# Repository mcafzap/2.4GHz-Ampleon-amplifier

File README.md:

# This amplifier is based on the Ampleon BCP2425M9X2S250-1 pallet

The bias circuit is taken from Ampleon's application note AN10900. There is an MSP430G2553 processor and an I2C 1.3" OLED display and 2 digital current monitors using the TLI4970. Unfortunately this current measurement device is end-of life, but it remains the best for resolving 6.25mA and measuring up to 25A. The display monitors voltage & current of each stage, sets the bias of each stage and shows the total power used.

Output protection is provided by a 100W isolator from Bert Modderman (pe1rki.com)
A 30v, 10A supply should give about 150W maximum - more than adequate for Q0-100 access. This pallet has 30dB of gain but a pre-amp will likely be required - the Amsat kit or a cheap shielded Chinese type. The circuit board uses an LM2596 dc-dc module. This can supply 12v for fans and/or the pre-amp or any voltage may be set to suit these devices. A lower voltage will lower the stress on the 3.3v linear regulator.

I used Kicad to draw/plot the circuit board and had them manufactured by JLCPCB. The program was written and tested on TI's Code Composer Studio but Energia may be used. 
The metal work was designed on FreeCAD and can be made from stock Al bar (10mm x 20mm) and Al sheet (2mm). The heatspreader is 10mm x 100mm x 72mm Cu. This is mounted on an Al heatsink approximately 250mm x 200mm x 40mm; it does not seem to require any fans.

Remember this is high frequency so everything must be kept short or shielded and properly 50 ohm terminated.

Thanks go to Vincent(M0LCR), Mike(G4VSS) and Brian(G4EWJ) for software/hardware advice but thanks are especially owed to Anthony Tognarelli of Waterfield Electronics Ltd. (waterfieldelectronics.com) for providing the pallets.

If I were to do this again? I'd simply use multi-turn presets to set the bias levels, (10K across a 3.3v supply). Much of the circuitry is concerned with displaying little-used data like power input and bias currents - once set, these are never changed.

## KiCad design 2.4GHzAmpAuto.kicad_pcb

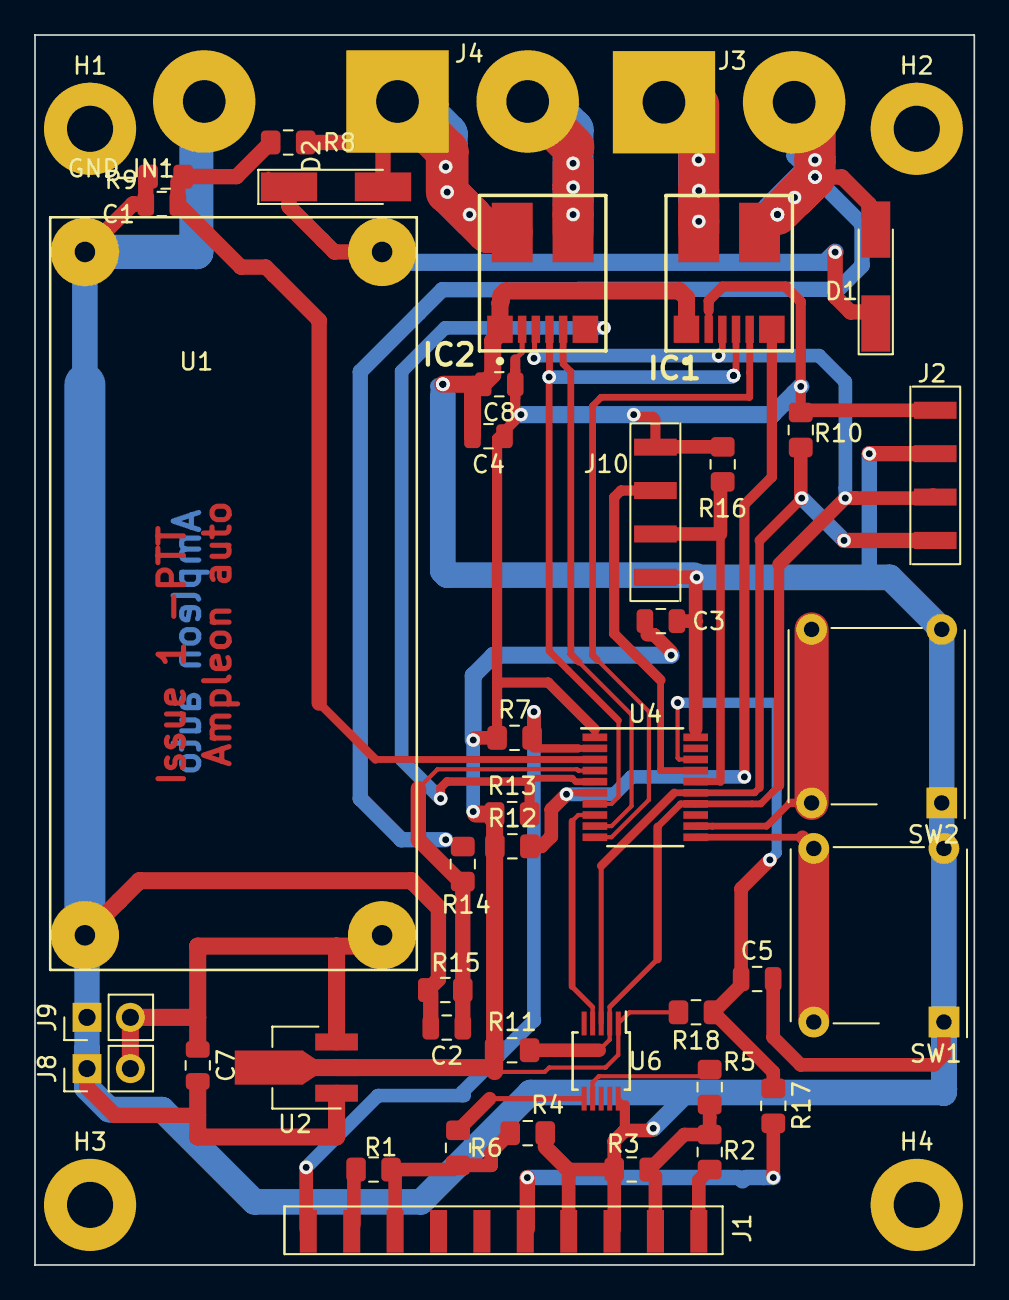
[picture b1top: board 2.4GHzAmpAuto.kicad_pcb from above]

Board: 2 copper layers, 55.0 x 72.0 mm, 47 parts (0 on the bottom side), 31 nets.

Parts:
C1, C2, C3, C4, C5, C8: 0u1; C_0805_2012Metric
C7: 10u; C_0805_2012Metric
D1, D2: D_ALT; D_MiniMELF_Handsoldering
GND_IN1: wire; SolderWirePad_1x01_Drill2.5mm
H1, H2, H3, H4: MountingHole_Pad; MountingHole_2.7mm_M2.5_Pad
IC1, IC2: TLI4970D025T5XUMA1; PG-TISON-8-1
J1: conections to module; Harwin_M20-89010xx_1x10_P2.54mm_Horizontal
J2: OLED; 1x04_P2.54mm_Pads
J3: current A; SolderWirePad_1x02_P7.62mm_Drill2.5mm
J4: current B; SolderWirePad_1x02_P7.62mm_Drill2.5mm
J8: Fan1; PinHeader_1x02_P2.54mm_Vertical
J9: Fan2; PinHeader_1x02_P2.54mm_Vertical
J10: program port; 1x04_P2.54mm_Pads
R1: 2K7; R_0805_2012Metric_Pad1.15x1.40mm_HandSolder
R2, R7: 1K5; R_0805_2012Metric_Pad1.15x1.40mm_HandSolder
R3: 1K0; R_0805_2012Metric_Pad1.15x1.40mm_HandSolder
R4: 4K3; R_0805_2012Metric_Pad1.15x1.40mm_HandSolder
R5, R17: K33; R_0805_2012Metric_Pad1.15x1.40mm_HandSolder
R6: K56; R_0805_2012Metric_Pad1.15x1.40mm_HandSolder
R8, R14: 33K; R_0805_2012Metric_Pad1.15x1.40mm_HandSolder
R9, R15: 2K2; R_0805_2012Metric_Pad1.15x1.40mm_HandSolder
R10, R11, R12, R13: 4K7; R_0805_2012Metric_Pad1.15x1.40mm_HandSolder
R16, R18: 10K; R_0805_2012Metric_Pad1.15x1.40mm_HandSolder
SW1, SW2: SW_Push; SW_MEC_5GTH9
U1: LM2596dcdc; LM2596_dc-dc_module
U2: AZ1117-3.3; SOT-89-3_Handsoldering
U4: MSP430G2553IPW20; TSSOP-20_4.4x6.5mm_P0.65mm
U6: MCP4728; MSOP-10_3x3mm_P0.5mm

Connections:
/12v: C7.1, J8.2, J9.2, U1.4, U2.3
/+3v3: C3.1, C4.1, C8.1, IC1.2, IC2.2, J2.1, J10.4, R7.1, R10.1, R11.1, R12.1, R13.1, R16.1, R18.2, U2.2, U4.1, U6.1
/GND: C1.2, C2.2, C3.2, C4.2, C5.2, C7.2, C8.2, GND_IN1.1, H1.1, H2.1, H3.1, H4.1, IC1.1, IC2.1, J1.3, J1.4, J2.2, J8.1, J9.1, J10.1, R3.2, R4.2, R9.2, R15.2, SW1.1, SW2.1, U1.2, U1.3, U2.1, U4.20, U6.10
/PTT: J1.5, R17.2
/T1: J1.1, R2.1
/T2: J1.9, R1.2
/T3: J1.10, R7.2, U4.2
/VG1: J1.2, R2.2, R3.1, R5.2
/VG2: J1.8, R1.1, R4.1, R6.2
/Vdd: D1.1, D2.1, U1.1
/reset: J10.2, R16.2, U4.16
/scl: IC1.3, IC2.3, J2.3, R11.2, U4.14, U6.2
/sda: J2.4, R10.2, U4.15, U6.3
/test: J10.3, U4.17
unnamed: C1.1, R8.2, R9.1, U4.3
unnamed: C2.1, R14.2, R15.1, U4.4
unnamed: C5.1, R17.1, R18.1, U4.18
unnamed: D1.2, IC1.7, J3.2, R14.1
unnamed: D2.2, IC2.8, J4.1, R8.1
unnamed: IC1.4, IC2.4, U4.7
unnamed: IC1.5, U4.10
unnamed: IC1.6, R12.2, U4.6
unnamed: IC1.8, J3.1
unnamed: IC2.5, U4.9
unnamed: IC2.6, R13.2, U4.5
unnamed: IC2.7, J4.2
unnamed: R5.1, U6.7
unnamed: R6.1, U6.6
unnamed: SW1.2, U4.11
unnamed: SW2.2, U4.12
unnamed: U4.8, U6.4
